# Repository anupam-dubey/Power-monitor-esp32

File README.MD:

# ESP32 Power monitoring and control   **updated     

### ESP32 as main role
### PZEM as modbus interface
### statemachine driven as per client read client data for more info 

PCB is inside KICAD@8.0.56 folder   
final code in pzem_iot.ino file   
report materrial is in reports section

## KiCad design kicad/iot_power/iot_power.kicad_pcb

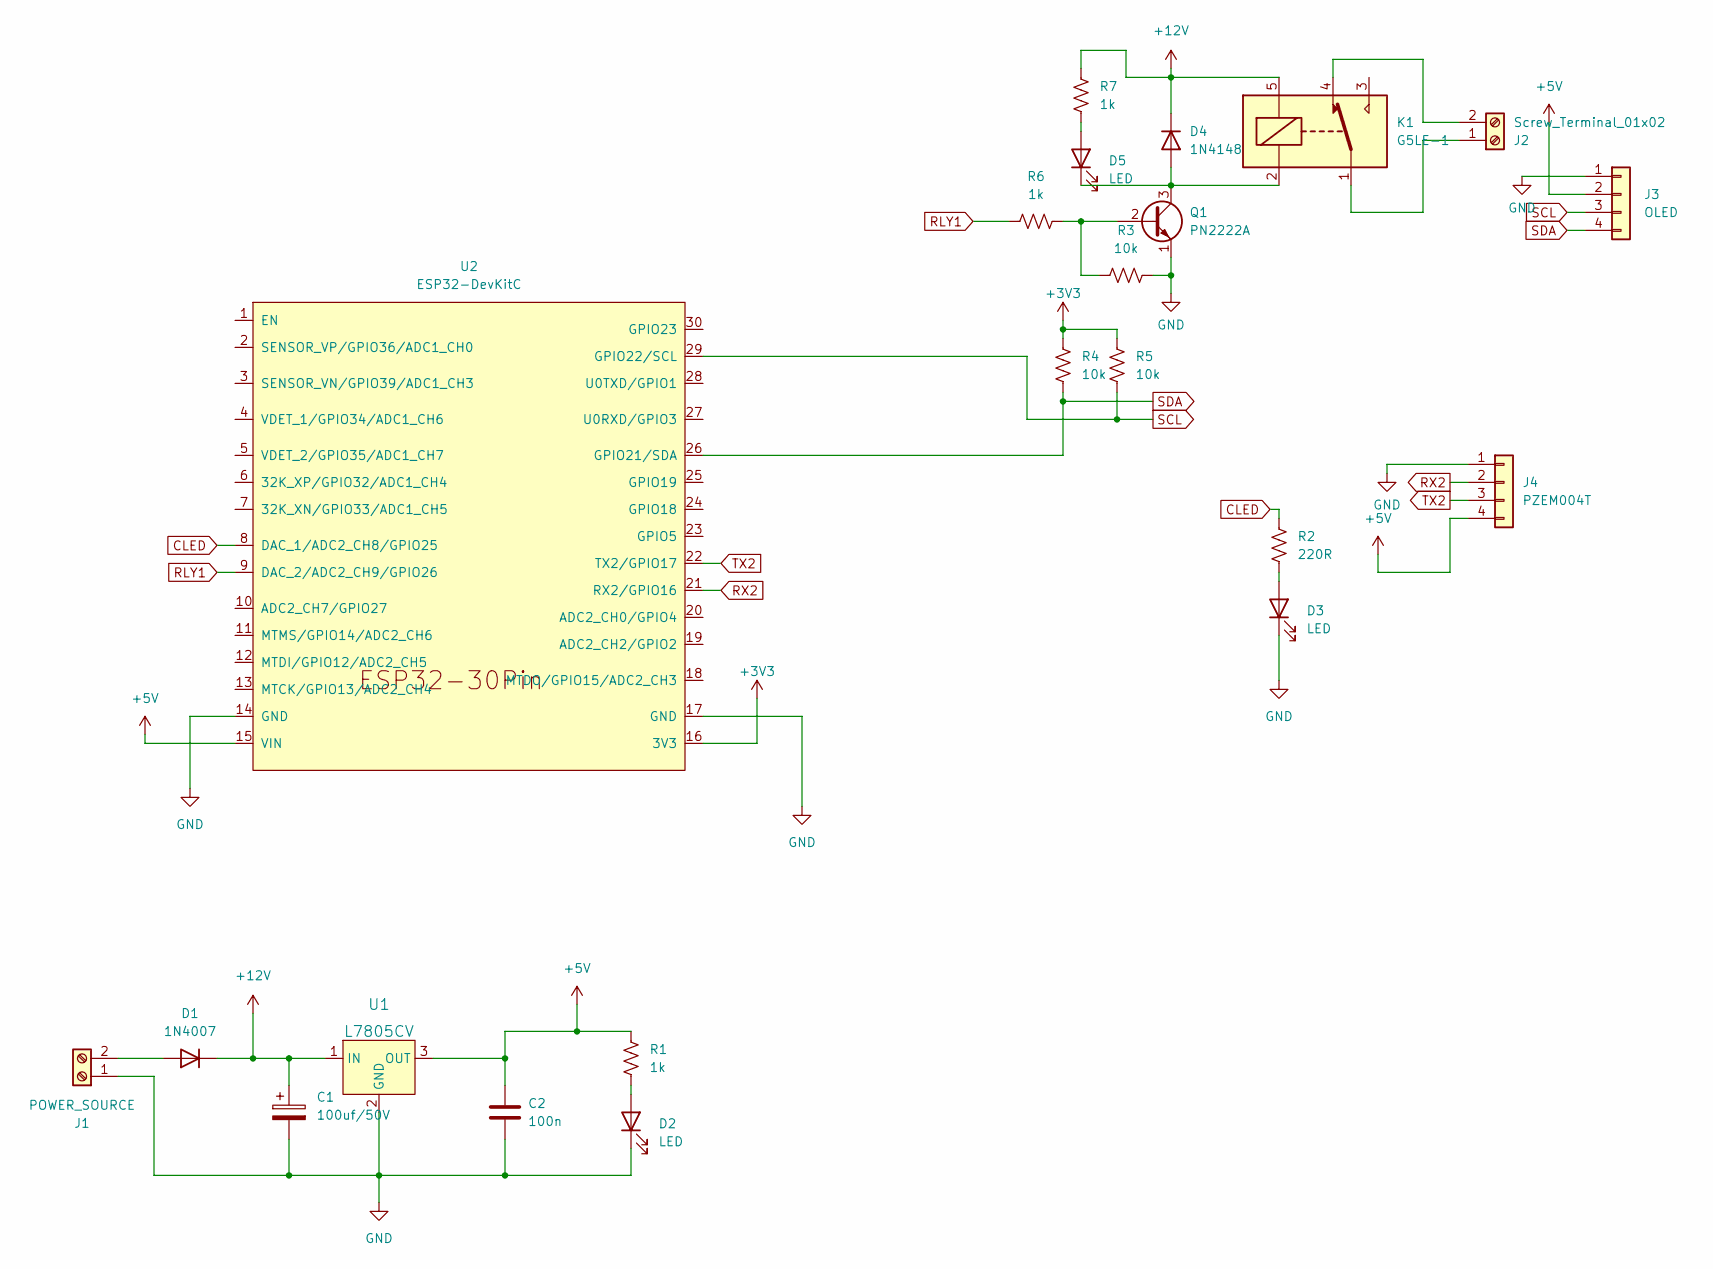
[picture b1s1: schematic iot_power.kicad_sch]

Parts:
C1: 100uf/50V; CP_Radial_D8.0mm_P3.80mm
C2: 100n; C_Disc_D4.3mm_W1.9mm_P5.00mm
D1: 1N4007; D_DO-41_SOD81_P10.16mm_Horizontal
D2, D5: LED; LED_D3.0mm
D3: LED; LED_D5.0mm_FlatTop
D4: 1N4148; D_DO-35_SOD27_P7.62mm_Horizontal
J1: POWER_SOURCE; TerminalBlock_Phoenix_MKDS-1,5-2-5.08_1x02_P5.08mm_Horizont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
J2: Screw_Terminal_01x02; TerminalBlock_Phoenix_MKDS-1,5-2-5.08_1x02_P5.08mm_Horizont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
J3: OLED; PinHeader_1x04_P2.54mm_Vertical
J4: PZEM004T; PinHeader_1x04_P2.54mm_Vertical
K1: G5LE-1; Relay_SPDT_Omron-G5LE-1
Q1: PN2222A; TO-92L_Inline_Wide
R1: 1k; R_Axial_DIN0204_L3.6mm_D1.6mm_P5.08mm_Horizontal
R2: 220R; R_Axial_DIN0207_L6.3mm_D2.5mm_P10.16mm_Horizontal
R3, R4, R5: 10k; R_Axial_DIN0207_L6.3mm_D2.5mm_P10.16mm_Horizontal
R6: 1k; R_Axial_DIN0207_L6.3mm_D2.5mm_P10.16mm_Horizontal
R7: 1k; R_Axial_DIN0207_L6.3mm_D2.5mm_P2.54mm_Vertical
U1: L7805CV; TO-220-3; MPN L7805CV; Digi-Key_PN 497-1443-5-ND
U2: ESP32-DevKitC; ESP32-Nodemcu-india_30pin

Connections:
+3V3: R4.1, R5.1, U2.16 (3V3)
+5V: C2.1, J3.2, J4.4, R1.1, U1.3 (OUT), U2.15 (VIN)
+12V: C1.1, D1.1 (K), D4.1 (K), K1.5, R7.1, U1.1 (IN)
CLED: R2.1, U2.8 (DAC_1/ADC2_CH8/GPIO25)
GND: C1.2, C2.2, D2.1 (K), D3.1 (K), J1.1, J3.1, J4.1, Q1.1 (E), R3.2, U1.2 (GND), U2.14 (GND), U2.17 (GND)
unnamed: D1.2 (A), J1.2
unnamed: D2.2 (A), R1.2
unnamed: D3.2 (A), R2.2
unnamed: D4.2 (A), D5.1 (K), K1.2, Q1.3 (C)
unnamed: D5.2 (A), R7.2
unnamed: J2.1, K1.1
unnamed: J2.2, K1.4
unnamed: Q1.2 (B), R3.1, R6.2
RLY1: R6.1, U2.9 (DAC_2/ADC2_CH9/GPIO26)
RX2: J4.2, U2.21 (RX2/GPIO16)
SCL: J3.3, R5.2, U2.29 (GPIO22/SCL)
SDA: J3.4, R4.2, U2.26 (GPIO21/SDA)
TX2: J4.3, U2.22 (TX2/GPIO17)

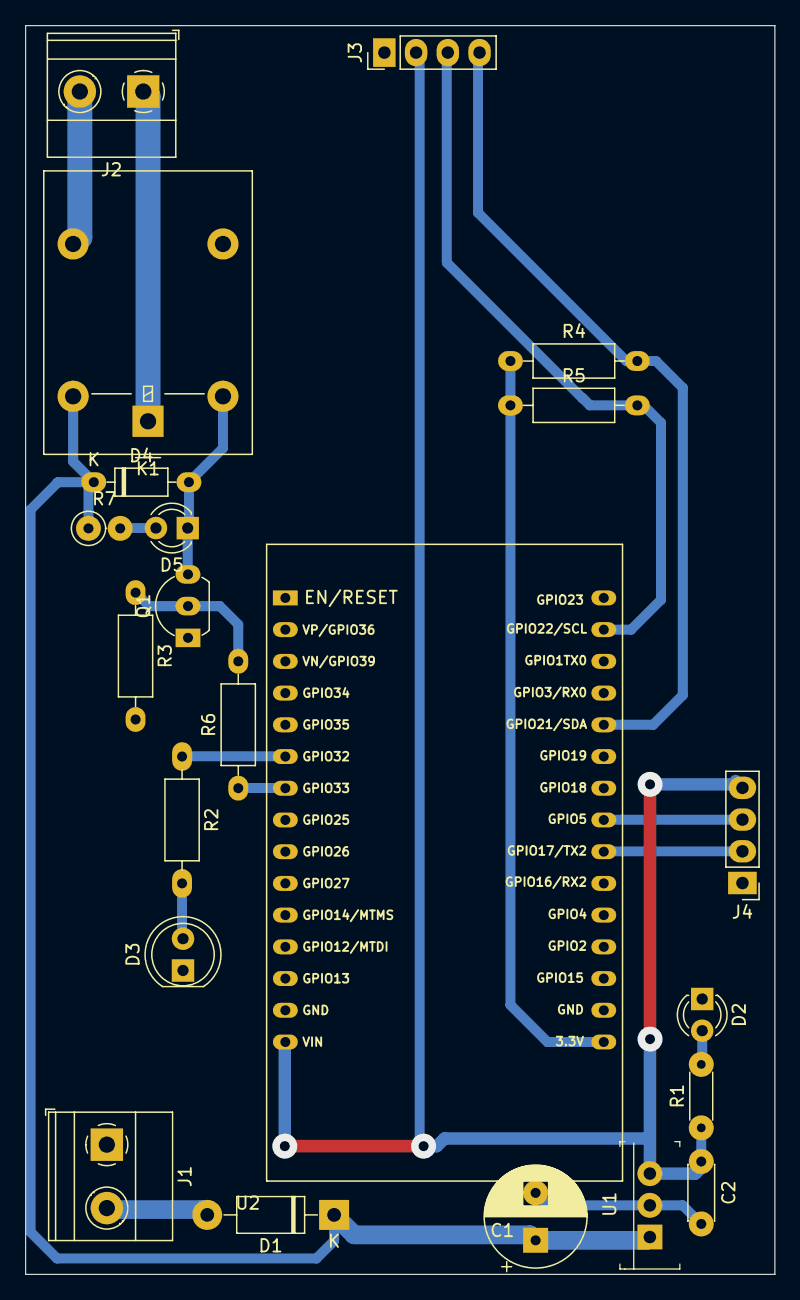
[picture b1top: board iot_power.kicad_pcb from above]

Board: 2 copper layers, 60.0 x 100.0 mm, 22 parts (0 on the bottom side), 18 nets.

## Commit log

2025-04-03 first
2025-11-07 nov 25
